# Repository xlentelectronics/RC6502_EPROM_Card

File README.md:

﻿﻿﻿﻿﻿﻿﻿﻿﻿﻿﻿﻿﻿﻿﻿﻿﻿﻿﻿﻿﻿# RC6502 EPROM CardThe RC6502 EPROM Card is a dedicated ROM add-on card designed to provide stable, non‑volatile program storage for the RC6502 Apple 1 Replica SBC. # How to BuildThe RC6502 EPROM Card has a few components. Of cours the EPROM it self, a 74LS138 address decoder to determine the card address, a switch or jumper, two 100nF decoupling capacitors, 10uF electrolyte capacitor and 39 pin edge connector.## ZIF SocketWhen you want to easy replace EPROM's or when you are in developing mode, it can be handy to install a ZIF socket. Unfortunately, a ZIF socket was not taken into account during the PCB design phase. However, you can still install a ZIF socket. This can be done in two ways, by placing the ZIF socket in an IC socket and mounting C2 flat, or by mounting the ZIF directly onto the PCB. In the latter case, it is more convenient to mount the Bank Select switch and C2 on the bottom side of the PCB.# Select EPROM Device The RC6502 EPROM Card supports multiple 32KB EPROM types, including the AT28C256, W27C256, W27E257, and the classic 27C256 UV‑EPROM. On the bottom side of the PCB, a set of solder jumpers determines which EPROM is installed. These jumpers configure the card for either an AT28C256 or a x27x256 EPROM. Select the correct jumper option to ensure proper working of the EPROM Card.On the bottom side of the PCB are two solder pads. By connecting the pads with a small dot of solder you select the used EPROM, AT28C256 or W27C256, W27E256, 27C256 type.# EPROM Card AddressThe EPROM card maps the EPROM cleanly into the upper memory region of the RC6502 Apple 1 Replica SBC address space, at base address $8000.  At the hardware level, the EPROM Card integrates seamlessly with the RC6502 backplane. Address decoding ensures that ROM is only active in the intended memory range, preventing bus conflicts with RAM or I/O devices. The board exposes a standard 28‑pin EPROM socket, allowing easy reprogramming and swapping of firmware during development. Because the card outputs stable, fast ROM reads, it is ideal for system monitors, bootloaders, BASIC interpreters, and custom firmware.# Bank SelectThe RC6502 EPROM Card divides the installed 32 KB EPROM into two independent 16 KB banks. The Bank Select switch determines which half of the EPROM is mapped into the CPU’s address space.When the switch is set to Bank 0, the EPROM exposes the first 16 KB block. When flipped to Bank 1, the card instead maps the second 16 KB block. Only one bank is active at a time, ensuring clean and conflict‑free memory decoding.This design allows you to store two separate firmware images inside a single EPROM, such as EhBASIC in Bank 0 and some other program in Bank 1. Switching between them requires no reprogramming: simply toggle the bank‑select switch and reset the system.# EhBASICA EhBASIC.bin file is available to fit in the EPROM card and to be run from address $8000.  When you have programed the Bin file in the EPROM, you run EhBASIC from EPROM by entering in WozMon **8000 R**.EhBASIC will start up with its regular Cold / warm message. Press C and enter a valid memory amount, mostly used is 20480.  ## WMON CommandThe EhBASIC version for the RC6502 has a command to switch back to WozMon. Enter at the EhBASIC prompt **WMON** to switch back to WozMon prompt.Just enter **8000 R** followed by W for Warm boot and you are back in EhBASIC. Your BASIC program will be still in memory and ready to use.  ## CLS CommandTo avoid every time typing a PRINT command with VT100 Escape sequins to clear the screen a new command CLS is available in this version of EhBASIC. # In practiceThe image shows an EPROM card with ZIF socket and with EhBASIC in the EPROM working together with the [RC6502 MC6821 PIA IO card](https://github.com/xlentelectronics/RC6502_MC6821_PIA_IO_Card).

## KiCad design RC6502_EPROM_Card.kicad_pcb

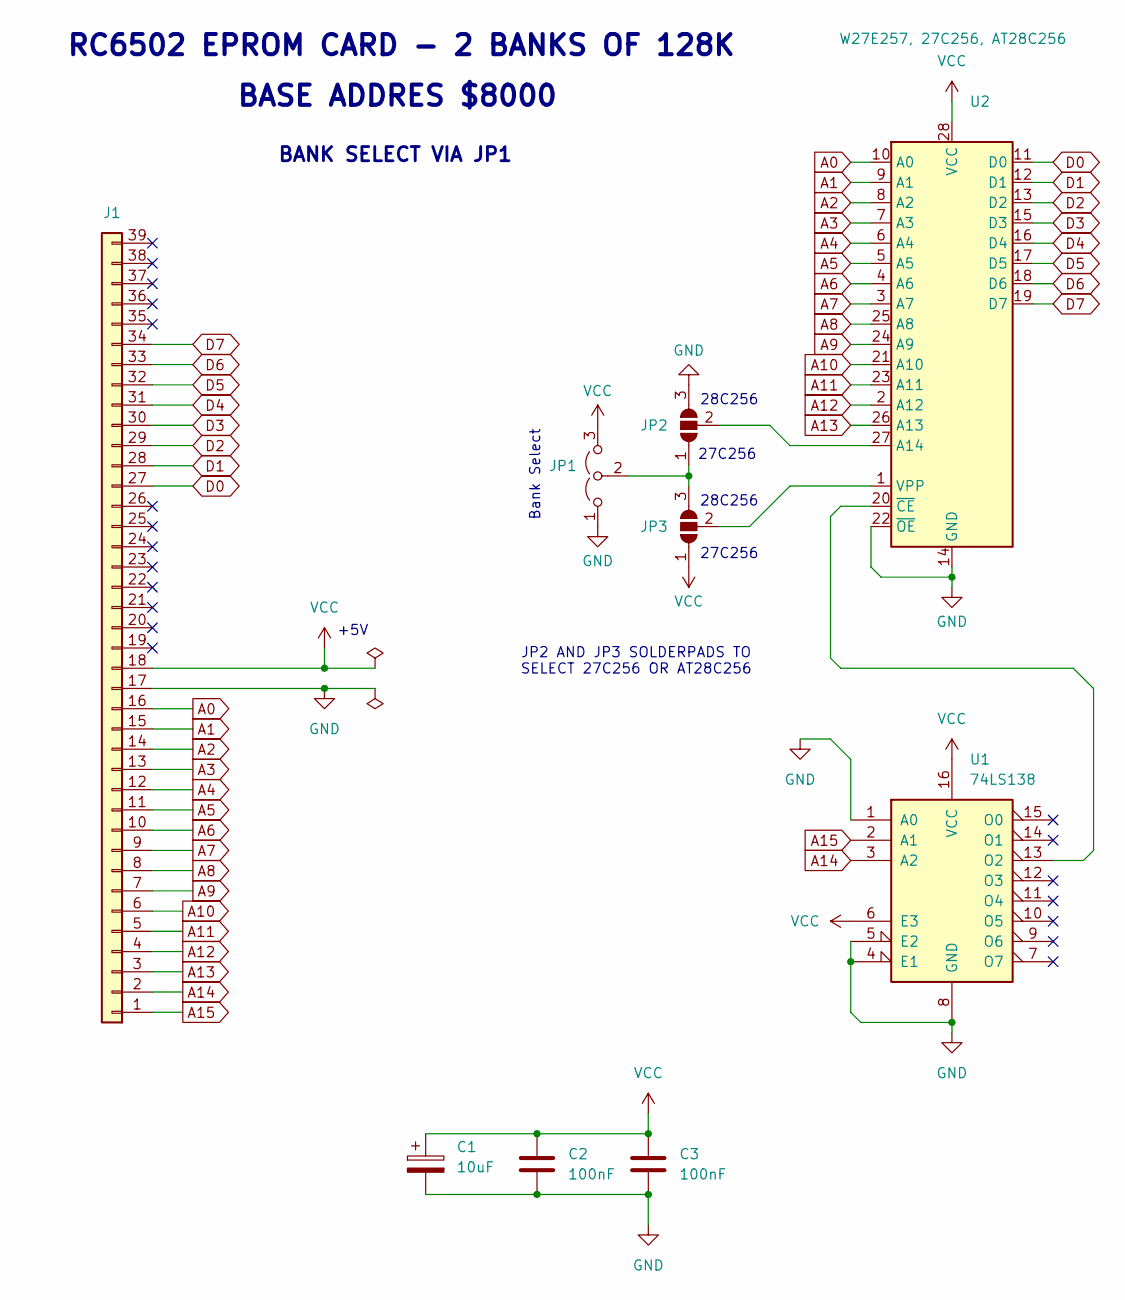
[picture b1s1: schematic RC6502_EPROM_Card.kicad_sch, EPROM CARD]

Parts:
C1: 10uF; CP_Radial_D6.3mm_P2.50mm
C2, C3: 100nF; C_Disc_D4.3mm_W1.9mm_P5.00mm
J1: Conn_01x39; PinHeader_1x39_P2.54mm_Horizontal
JP1: Jumper_3_Open; PinHeader_1x03_P2.54mm_Vertical
JP2, JP3: SolderJumper_3_Open; SolderJumper-3_P1.3mm_Open_RoundedPad1.0x1.5mm
U1: 74LS138; DIP-16_W7.62mm
U2: W27E257, 27C256, AT28C256; DIP-28_W15.24mm

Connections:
A0: J1.16, U2.10 (A0)
A1: J1.15, U2.9 (A1)
A2: J1.14, U2.8 (A2)
A3: J1.13, U2.7 (A3)
A4: J1.12, U2.6 (A4)
A5: J1.11, U2.5 (A5)
A6: J1.10, U2.4 (A6)
A7: J1.9, U2.3 (A7)
A8: J1.8, U2.25 (A8)
A9: J1.7, U2.24 (A9)
A10: J1.6, U2.21 (A10)
A11: J1.5, U2.23 (A11)
A12: J1.4, U2.2 (A12)
A13: J1.3, U2.26 (A13)
A14: J1.2, U1.3 (A2)
A15: J1.1, U1.2 (A1)
D0: J1.27, U2.11 (D0)
D1: J1.28, U2.12 (D1)
D2: J1.29, U2.13 (D2)
D3: J1.30, U2.15 (D3)
D4: J1.31, U2.16 (D4)
D5: J1.32, U2.17 (D5)
D6: J1.33, U2.18 (D6)
D7: J1.34, U2.19 (D7)
GND: C1.2, C2.2, C3.2, J1.17, JP1.1 (A), JP2.3 (B), U1.1 (A0), U1.4 (E1), U1.5 (E2), U1.8 (GND), U2.14 (GND), U2.22 (~OE)
unnamed: JP1.2 (C), JP2.1 (A), JP3.3 (B)
unnamed: JP2.2 (C), U2.27 (A14)
unnamed: JP3.2 (C), U2.1 (VPP)
unnamed: U1.13 (O2), U2.20 (~CE)
VCC: C1.1, C2.1, C3.1, J1.18, JP1.3 (B), JP3.1 (A), U1.6 (E3), U1.16 (VCC), U2.28 (VCC)

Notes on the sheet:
28C256
Bank Select
27C256
BANK SELECT VIA JP1
BASE ADDRES $8000
RC6502 EPROM CARD - 2 BANKS OF 128K
+5V
JP2 AND JP3 SOLDERPADS TO SELECT 27C256 OR AT28C256

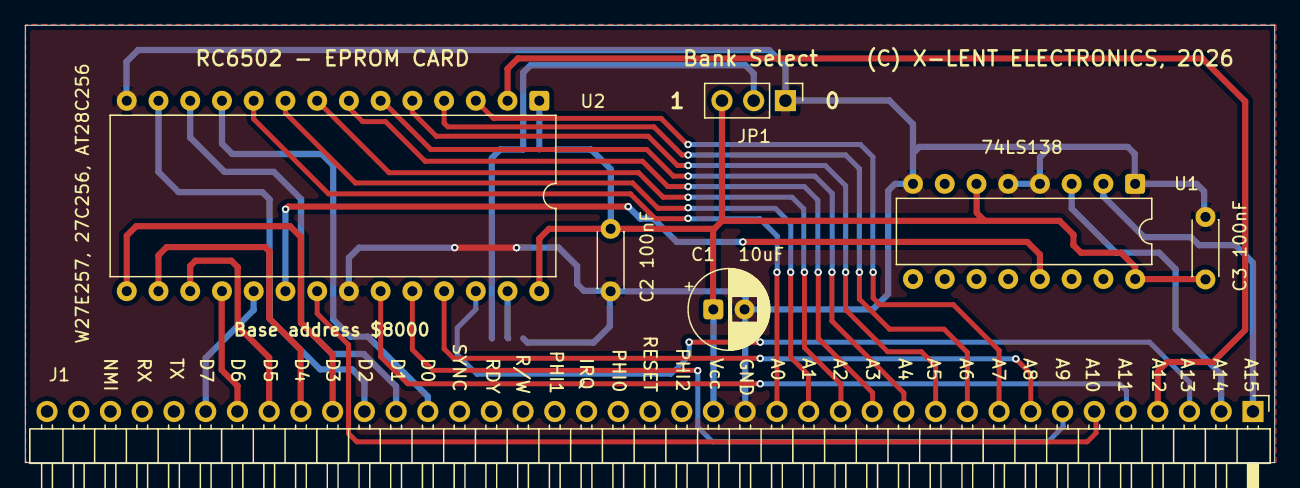
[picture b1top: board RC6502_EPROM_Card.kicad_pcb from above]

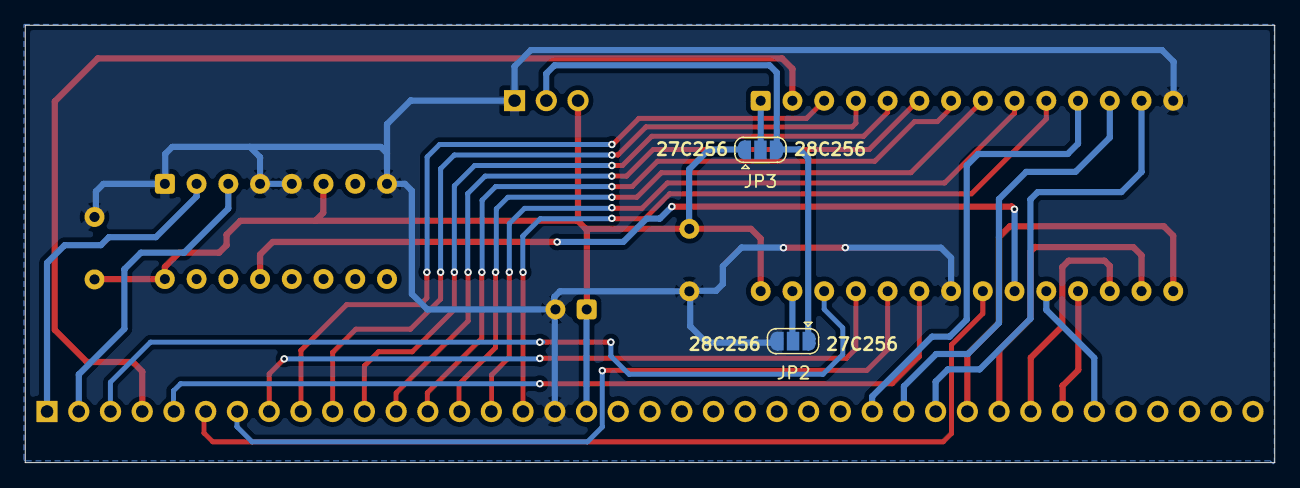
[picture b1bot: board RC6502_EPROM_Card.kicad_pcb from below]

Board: 2 copper layers, 100.0 x 35.0 mm, 9 parts (2 on the bottom side), 30 nets.

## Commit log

2026-05-19 Rename Xlent_EhBASIC.jpg to XLENT_EhBASIC.jpg
